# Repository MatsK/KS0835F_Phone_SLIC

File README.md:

# KS0835F_Phone_SLIC

KS0835F phone line SLIC module breakout PCB

This PCB includes the recommended support circuitry for the subscriber line interface and provides an RJ phone jack, and a header for providing power, control I/O, and audio in/out.

## Interactive BOM

[Interactive Bill Of Material, BOM](https://matsk.github.io/KS0835F_Phone_SLIC/ibom.html)

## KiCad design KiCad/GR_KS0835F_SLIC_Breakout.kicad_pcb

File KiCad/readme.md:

# KiCAD version

The Schema and PCB Design files are in KiCAD version 9 format

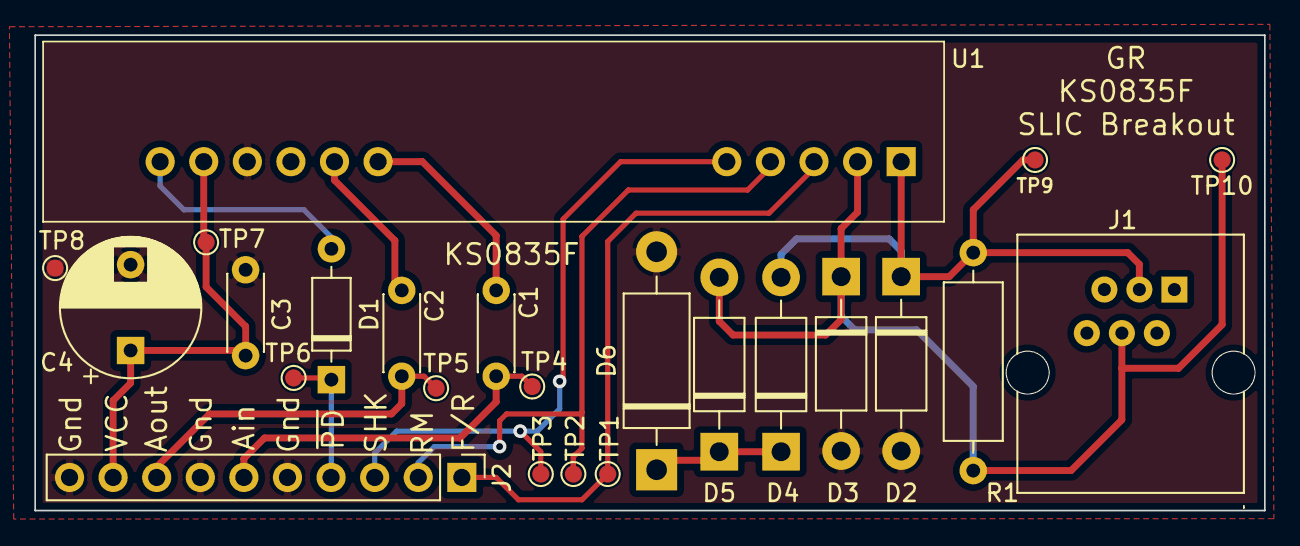
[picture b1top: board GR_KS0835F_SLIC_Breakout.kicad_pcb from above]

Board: 2 copper layers, 71.7 x 27.7 mm, 24 parts (0 on the bottom side), 14 nets.

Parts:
C1, C2, C3: 100nF; C_Disc_D4.3mm_W1.9mm_P5.00mm
C4: 10uF 16v; CP_Radial_D8.0mm_P5.00mm
D1: 1N4148; D_DO-35_SOD27_P7.62mm_Horizontal
D2, D3, D4, D5: 1N4004; D_DO-41_SOD81_P10.16mm_Horizontal
D6: P6KE82; D_DO-15_P12.70mm_Horizontal
J1: RJ; RJ_6p6c
J2: Conn_01x10; PinHeader_1x10_P2.54mm_Vertical
R1: 1 MEG; R_Axial_DIN0309_L9.0mm_D3.2mm_P12.70mm_Horizontal
TP1, TP2, TP3, TP4, TP5, TP6, TP7, TP8, TP9, TP10: TestPoint; TestPoint_Pad_D1.0mm
U1: KS0835F

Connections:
/Ain: C1.1, J2.6, TP4.1
/Aout: C2.1, J2.8, TP5.1
/F_R: J2.1, TP1.1, U1.3
/RM: J2.2, TP2.1, U1.4
/SHK: J2.3, TP3.1, U1.5
/~PD: D1.1, J2.4, TP6.1
GNDREF: C3.2, C4.2, D2.2, D3.2, D6.2, J2.5, J2.7, J2.10, TP8.1, U1.9
unnamed: C1.2, U1.6
unnamed: C2.2, U1.7
unnamed: D1.2, U1.11
unnamed: D2.1, D4.2, J1.3, R1.2, TP9.1, U1.1
unnamed: D3.1, D5.2, J1.4, R1.1, TP10.1, U1.2
unnamed: D4.1, D5.1, D6.1
VCC: C3.1, C4.1, J2.9, TP7.1, U1.10

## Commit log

2025-05-05 Update readme.md
    Added KiCAD version
2025-05-05 Added an interactive BOM file
2025-05-05 Restructuring and added a iBOM
2025-05-05 Update README.md
    Trying to gat ibom.html working
